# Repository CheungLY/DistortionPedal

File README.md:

# DistortionPedal
A pedal that uses diode clipping to generate light distortion in a circuit.

To do this I followed this guide: https://curiousmotor.com/2019/12/07/distortion-pedal-electronics-explained/ and added a few modifications.

This is the what the schematic looks like which can be divided into 3 sections:

On the left is the input section:
This is just the part where the signal (in the form of an alternating current enters)

The middle section is the amplicification stage:
This part sends the signal through a transistor which amplifies it and leads it go to out, the output jack

The top section is clipping or fxIn and fxOut:
The diodes clip the amplitude to about 0.7v which is then amplified in the system.

This is the look of the PCB

And this is the 3D model:

The Gerber is attached in the Distortion pedal.zip and schematic with PCB as well.

The only specifically unique component is the 3PDT STOMP SWITCH, Kicad inherintly does not have this switch so you may need to design one yourself using the different symbols for SPDT switches. This is a specific switch used in most pedals

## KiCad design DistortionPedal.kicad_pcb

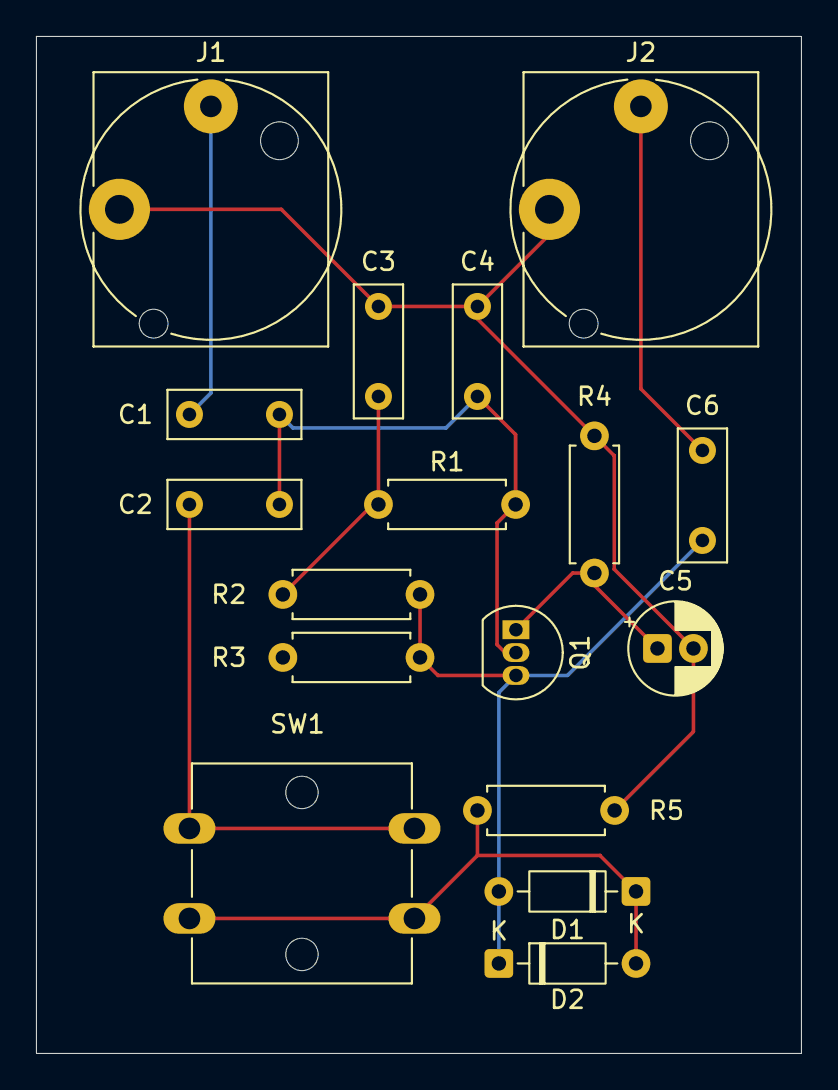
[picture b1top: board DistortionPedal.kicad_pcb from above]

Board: 2 copper layers, 42.5 x 56.5 mm, 17 parts (0 on the bottom side), 9 nets.

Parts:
C1, C2, C6: 0.1uF; C_Rect_L7.2mm_W2.5mm_P5.00mm
C3: 0.01uF; C_Rect_L7.2mm_W2.5mm_P5.00mm
C4: 0.001uF; C_Rect_L7.2mm_W2.5mm_P5.00mm
C5: 22uF; CP_Radial_D5.0mm_P2.00mm
D1, D2: D; D_DO-35_SOD27_P7.62mm_Horizontal
J1, J2: AudioJack2; Jack_6.35mm_Neutrik_NJ2FD-V_Vertical
Q1: 2N3904; TO-92_Inline
R1, R2: 220k; R_Axial_DIN0207_L6.3mm_D2.5mm_P7.62mm_Horizontal
R3: 68k; R_Axial_DIN0207_L6.3mm_D2.5mm_P7.62mm_Horizontal
R4: 680; R_Axial_DIN0207_L6.3mm_D2.5mm_P7.62mm_Horizontal
R5: 1M; R_Axial_DIN0207_L6.3mm_D2.5mm_P7.62mm_Horizontal
SW1: SW_SPST; SW_SPST_Omron_B3F-40xx

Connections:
/FxIn: C1.2, C4.1, Q1.2 (B), R1.2
/FxOut: C6.1, Q1.3 (C), R2.1, R3.1
GND: C3.2, C4.2, C5.2, J1.S, J2.S, R4.2, R5.2
unnamed: C1.1, J1.T
unnamed: C3.1, R1.1, R2.2
unnamed: C6.2, J2.T
unnamed: D1.2 (A), D2.1 (K)
unnamed: C2.1, D1.1 (K), D2.2 (A), R5.1, SW1.2 (B)
unnamed: C5.1, Q1.1 (E), R4.1
